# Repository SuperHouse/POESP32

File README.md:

ESP32 Controller with Ethernet and PoE
======================================
Copyright 2018 SuperHouse Automation Pty Ltd  www.superhouse.tv  

ESP32 controller board with Ethernet and PoE support.

Includes 2 x I/O Breakout headers (12-pin IDC) compatible with other
I/O Breakout boards from SuperHouse.

More information is available at:

  http://www.superhouse.tv/poesp32

INSTALLATION
------------
The design is saved as an EAGLE project. EAGLE PCB design software is
available from www.cadsoftusa.com free for non-commercial use. To use
this project download it and place the directory containing these files
into the "eagle" directory on your computer. Then open EAGLE and
navigate to the project.

DISTRIBUTION
------------
The specific terms of distribution of this project are governed by the
license referenced below.

LICENSE
-------
Licensed under the TAPR Open Hardware License (www.tapr.org/OHL).
The "license" folder within this repository also contains a copy of
this license in plain text format.

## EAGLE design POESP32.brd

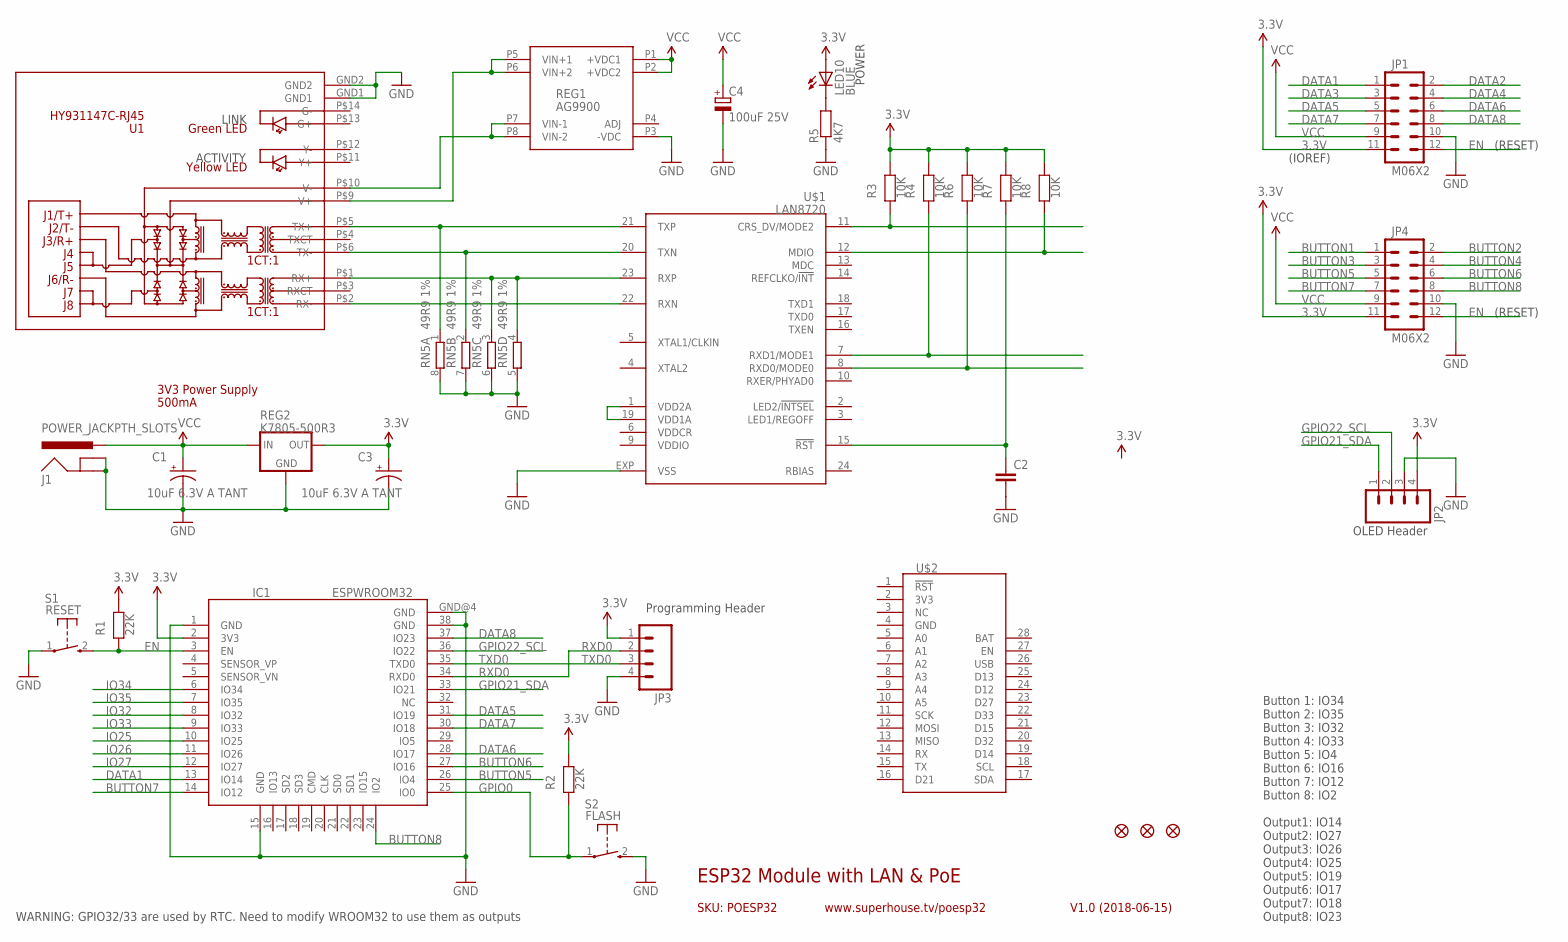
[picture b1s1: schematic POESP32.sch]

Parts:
C1, C3: 10uF 6.3V A TANT; EIA3216
C2: CAP0805; 0805
C4: 100uF 25V; PANASONIC_D
FID1, FID2, FID3: FIDUCIAL1X2.5; FIDUCIAL-1X2.5
IC1: ESPWROOM32
J1: POWER_JACKPTH_SLOTS; POWER_JACK_PTH_SLOTS
JP1, JP4: M06X2; 2X6-SHROUDED
JP2, JP3: M04PTH; 1X04
LED10: BLUE; LED-0603
R1, R2: 22K; 0603@2
R3, R4, R6, R7, R8: 10K; 0603@2
R5: 4K7; 0603
REG1: AG9900
REG2: K7805-500R3; K78XX-500R3
RN5: 49R9 1%; CAY16
S1: RESET; TACTILE_SWITCH_SMD_2PIN_TINY
S2: FLASH; TACTILE_SWITCH_SMD_2PIN_TINY
U1: HY931147C-RJ45; HY931147C
U$1: LAN8720; QFN24
U$2: FEATHER

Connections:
3.3V: C3.A (+), IC1.2 (3V3), JP1.11, JP2.4, JP3.1, JP4.11, LED10.A, R1.1, R2.1, R3.1, R4.1, R6.1, R7.1, R8.1, REG2.3 (OUT)
BUTTON1: JP4.1
BUTTON2: JP4.2
BUTTON3: JP4.3
BUTTON4: JP4.4
BUTTON5: IC1.26 (IO4), JP4.5
BUTTON6: IC1.27 (IO16), JP4.6
BUTTON7: IC1.14 (IO12), JP4.7
BUTTON8: IC1.24 (IO2), JP4.8
DATA1: IC1.13 (IO14), JP1.1
DATA2: JP1.2
DATA3: JP1.3
DATA4: JP1.4
DATA5: IC1.31 (IO19), JP1.5
DATA6: IC1.28 (IO17), JP1.6
DATA7: IC1.30 (IO18), JP1.7
DATA8: IC1.37 (IO23), JP1.8
EN: IC1.3 (EN), JP1.12, JP4.12, R1.2, S1.2 (S)
GND: C1.C (-), C2.2, C3.C (-), C4.-, IC1.1 (GND), IC1.15 (GND), IC1.38 (GND), IC1.GND@4 (GND), J1.GND, J1.GNDBREAK, JP1.10, JP2.3, JP3.4, JP4.10, R5.1, REG1.P3 (-VDC), REG2.2 (GND), RN5.5 (2), RN5.6 (2), RN5.7 (2), RN5.8 (2), S1.1, S2.2 (S), U1.GND1, U1.GND2, U$1.EXP (VSS)
GPIO0: IC1.25 (IO0), R2.2, S2.1
GPIO21_SDA: IC1.33 (IO21), JP2.1
GPIO22_SCL: IC1.36 (IO22), JP2.2
IO25: IC1.10 (IO25)
IO26: IC1.11 (IO26)
IO27: IC1.12 (IO27)
IO32: IC1.8 (IO32)
IO33: IC1.9 (IO33)
IO34: IC1.6 (IO34)
IO35: IC1.7 (IO35)
unnamed: RN5.1, U1.P$5 (TX+), U$1.21 (TXP)
unnamed: REG1.P5 (VIN+1), REG1.P6 (VIN+2), U1.P$9 (V+)
unnamed: REG1.P7 (VIN-1), REG1.P8 (VIN-2), U1.P$10 (V-)
unnamed: RN5.2 (1), U1.P$6 (TX-), U$1.20 (TXN)
unnamed: RN5.3 (1), RN5.4 (1), U1.P$1 (RX+), U$1.23 (RXP)
unnamed: U1.P$2 (RX-), U$1.22 (RXN)
unnamed: U$1.1 (VDD2A), U$1.19 (VDD1A)
unnamed: R4.2, U$1.7 (RXD1/MODE1)
unnamed: R6.2, U$1.8 (RXD0/MODE0)
unnamed: R3.2, U$1.11 (CRS_DV/MODE2)
unnamed: C2.1, R7.2, U$1.15 (!RST)
unnamed: R8.2, U$1.12 (MDIO)
unnamed: LED10.C, R5.2
RXD0: IC1.34 (RXD0), JP3.2
TXD0: IC1.35 (TXD0), JP3.3
VCC: C1.A (+), C4.+, J1.PWR, JP1.9, JP4.9, REG1.P1 (+VDC1), REG1.P2 (+VDC2), REG2.1 (IN)
VDDCR: U$1.6 (VDDCR)
VDDIO: U$1.9 (VDDIO)

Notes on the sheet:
SKU: POESP32
ESP32 Module with LAN & PoE
V1.0 (2018-06-15)
www.superhouse.tv/poesp32
Button 1: IO34 Button 2: IO35 Button 3: IO32 Button 4: IO33 Button 5: IO4 Button 6: IO16 Button 7: IO12 Button 8: IO2 Output1: IO14 Output2: IO27 Output3: IO26 Output4: IO25 Output5: IO19 Output6: IO17 Output7: IO18 Output8: IO23
POWER
3V3 Power Supply
500mA
(IOREF)
WARNING: GPIO32/33 are used by RTC. Need to modify WROOM32 to use them as outputs
OLED Header
Programming Header
(RESET)
LINK
ACTIVITY

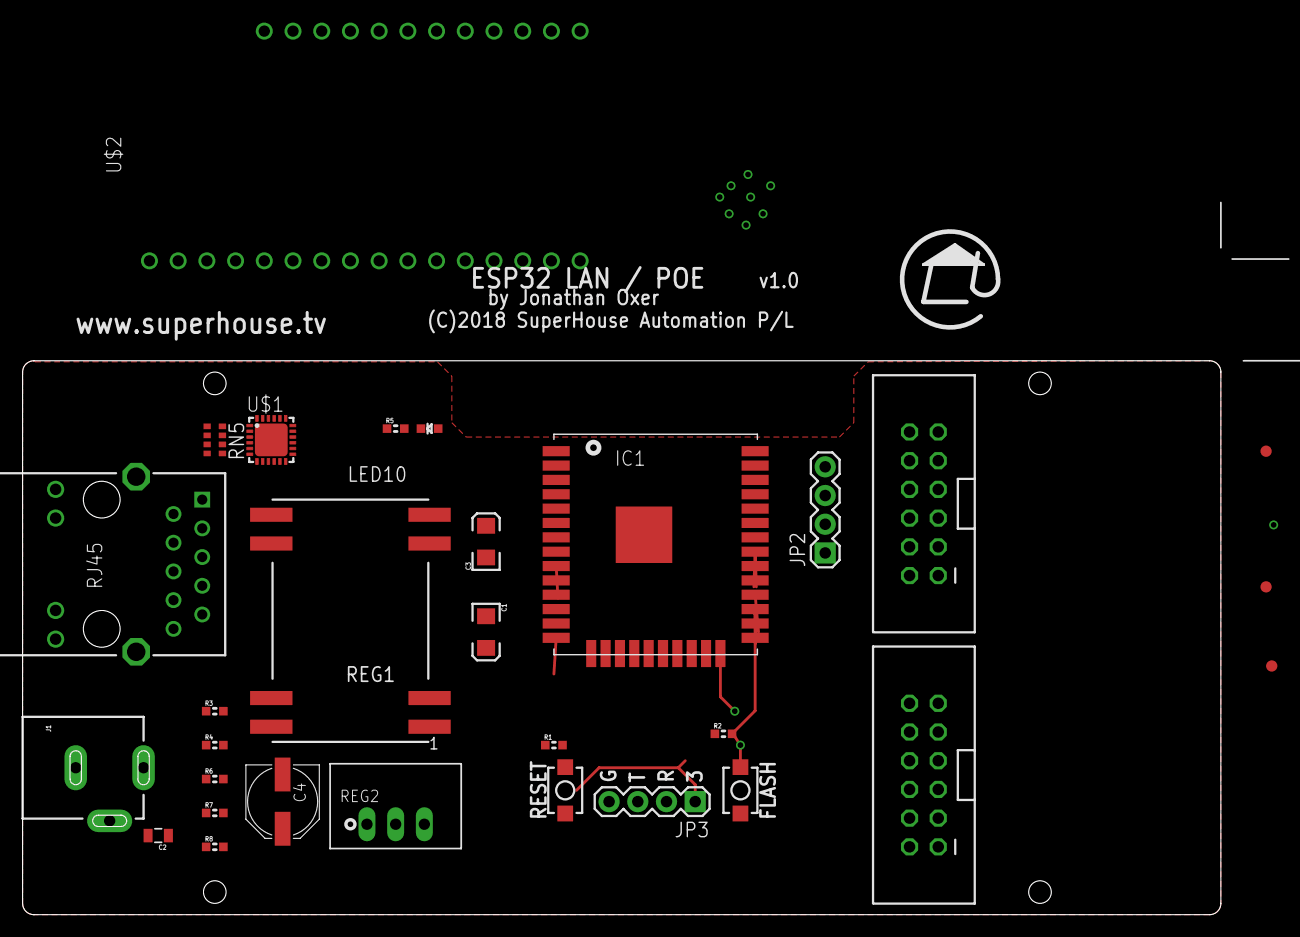
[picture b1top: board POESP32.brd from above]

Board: 2 copper layers, 106.0 x 49.0 mm, 30 parts (0 on the bottom side), 31 nets.

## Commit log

2019-04-24 Import of rough draft files

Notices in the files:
POESP32.brd:
(C)2018 SuperHouse Automation P/L
parts and their libraries:
microchip-smsc-lan8720: (C) 2014 Tomasz Boleslaw CEDRO, cederom@tlen.pl, http://www.tomek.cedro.info.
freetronics-original: Licensing: CC v3.0 Share-Alike You are welcome to use this library for commercial purposes.
